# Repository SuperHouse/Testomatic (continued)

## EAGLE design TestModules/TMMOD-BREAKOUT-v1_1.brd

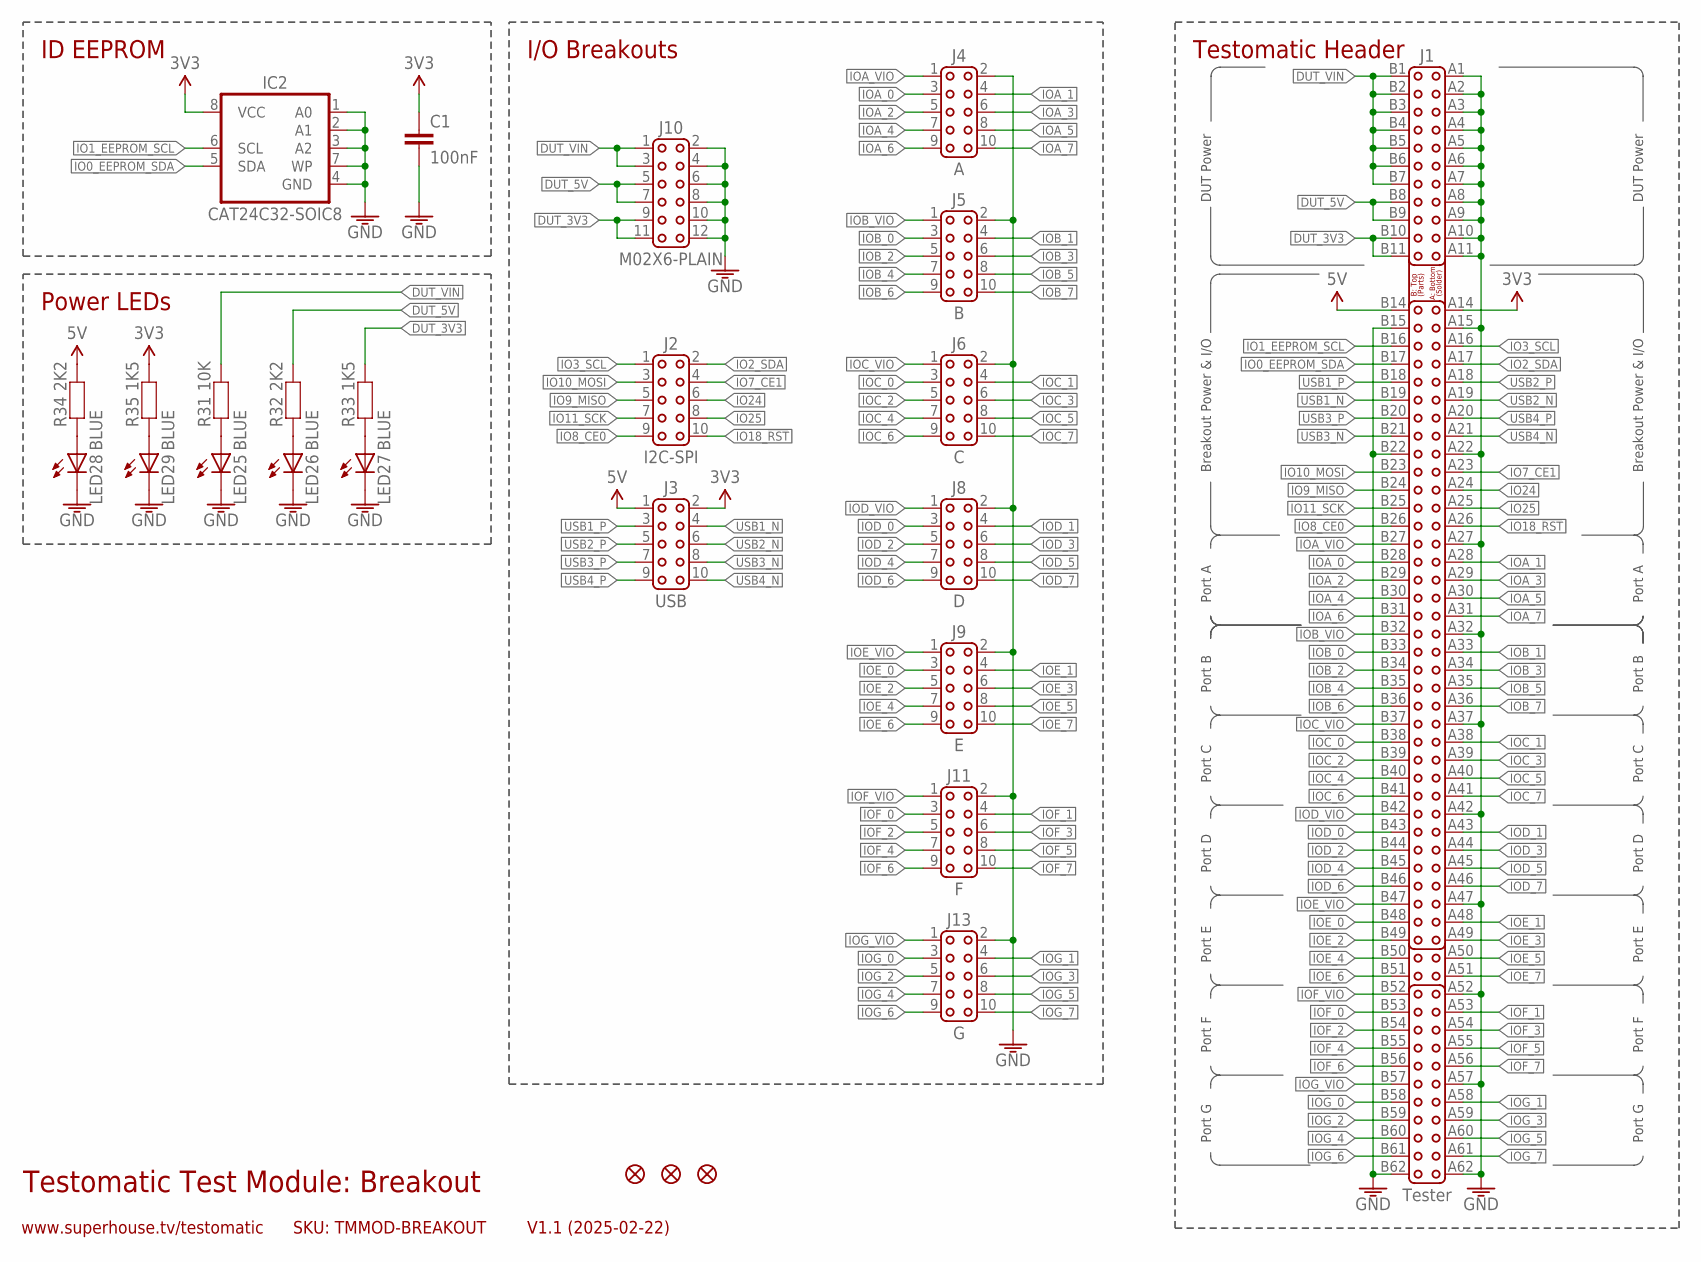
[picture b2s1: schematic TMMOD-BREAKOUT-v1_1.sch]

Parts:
C1: 100nF; C0603
FID1, FID2, FID3: FIDUCIAL1X2.5; FIDUCIAL-1X2.5
IC2: CAT24C32-SOIC8; SOIC8
J1: Tester; PCI-CARD
J2: I2C-SPI; 2X05-2.54-PLAIN
J3: USB; 2X05-2.54-PLAIN
J4: A; 2X05-2.54-PLAIN
J5: B; 2X05-2.54-PLAIN
J6: C; 2X05-2.54-PLAIN
J8: D; 2X05-2.54-PLAIN
J9: E; 2X05-2.54-PLAIN
J10: M02X6-PLAIN; 2X06
J11: F; 2X05-2.54-PLAIN
J13: G; 2X05-2.54-PLAIN
LED25, LED26, LED27, LED28, LED29: BLUE; LED-0603
R31: 10K; R0603
R32, R34: 2K2; R0603
R33, R35: 1K5; R0603

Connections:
3.3V: C1.1, IC2.8 (VCC), J1.A14, J3.2, R35.2
5V: J1.B14, J3.1, R34.2
DUT_3V3: J1.B10, J1.B11, J10.9, J10.11, R33.2
DUT_5V: J1.B8, J1.B9, J10.5, J10.7, R32.2
DUT_VIN: J1.B1, J1.B2, J1.B3, J1.B4, J1.B5, J1.B6, J1.B7, J10.1, J10.3, R31.2
GND: C1.2, IC2.1 (A0), IC2.2 (A1), IC2.3 (A2), IC2.4 (GND), IC2.7 (WP), J1.A1, J1.A2, J1.A3, J1.A4, J1.A5, J1.A6, J1.A7, J1.A8, J1.A9, J1.A10, J1.A11, J1.A15, J1.A22, J1.A27, J1.A32, J1.A37, J1.A42, J1.A47, J1.A52, J1.A57, J1.A62, J1.B15, J1.B22, J1.B62, J4.2, J5.2, J6.2, J8.2, J9.2, J10.2, J10.4, J10.6, J10.8, J10.10, J10.12, J11.2, J13.2, LED25.C, LED26.C, LED27.C, LED28.C, LED29.C
IO0_EEPROM_SDA: IC2.5 (SDA), J1.B17
IO1_EEPROM_SCL: IC2.6 (SCL), J1.B16
IO2_SDA: J1.A17, J2.2
IO3_SCL: J1.A16, J2.1
IO7_CE1: J1.A23, J2.4
IO8_CE0: J1.B26, J2.9
IO9_MISO: J1.B24, J2.5
IO10_MOSI: J1.B23, J2.3
IO11_SCK: J1.B25, J2.7
IO18_!RST: J1.A26, J2.10
IO24: J1.A24, J2.6
IO25: J1.A25, J2.8
IOA_0: J1.B28, J4.3
IOA_1: J1.A28, J4.4
IOA_2: J1.B29, J4.5
IOA_3: J1.A29, J4.6
IOA_4: J1.B30, J4.7
IOA_5: J1.A30, J4.8
IOA_6: J1.B31, J4.9
IOA_7: J1.A31, J4.10
IOA_VIO: J1.B27, J4.1
IOB_0: J1.B33, J5.3
IOB_1: J1.A33, J5.4
IOB_2: J1.B34, J5.5
IOB_3: J1.A34, J5.6
IOB_4: J1.B35, J5.7
IOB_5: J1.A35, J5.8
IOB_6: J1.B36, J5.9
IOB_7: J1.A36, J5.10
IOB_VIO: J1.B32, J5.1
IOC_0: J1.B38, J6.3
IOC_1: J1.A38, J6.4
IOC_2: J1.B39, J6.5
IOC_3: J1.A39, J6.6
IOC_4: J1.B40, J6.7
IOC_5: J1.A40, J6.8
IOC_6: J1.B41, J6.9
IOC_7: J1.A41, J6.10
IOC_VIO: J1.B37, J6.1
IOD_0: J1.B43, J8.3
IOD_1: J1.A43, J8.4
IOD_2: J1.B44, J8.5
IOD_3: J1.A44, J8.6
IOD_4: J1.B45, J8.7
IOD_5: J1.A45, J8.8
IOD_6: J1.B46, J8.9
IOD_7: J1.A46, J8.10
IOD_VIO: J1.B42, J8.1
IOE_0: J1.B48, J9.3
IOE_1: J1.A48, J9.4
IOE_2: J1.B49, J9.5
IOE_3: J1.A49, J9.6
IOE_4: J1.B50, J9.7
IOE_5: J1.A50, J9.8
IOE_6: J1.B51, J9.9
IOE_7: J1.A51, J9.10
IOE_VIO: J1.B47, J9.1
IOF_0: J1.B53, J11.3
IOF_1: J1.A53, J11.4
IOF_2: J1.B54, J11.5
IOF_3: J1.A54, J11.6
IOF_4: J1.B55, J11.7
IOF_5: J1.A55, J11.8
IOF_6: J1.B56, J11.9
IOF_7: J1.A56, J11.10
IOF_VIO: J1.B52, J11.1
IOG_0: J1.B58, J13.3
IOG_1: J1.A58, J13.4
IOG_2: J1.B59, J13.5
IOG_3: J1.A59, J13.6
IOG_4: J1.B60, J13.7
IOG_5: J1.A60, J13.8
IOG_6: J1.B61, J13.9
IOG_7: J1.A61, J13.10
IOG_VIO: J1.B57, J13.1
unnamed: LED25.A, R31.1
unnamed: LED28.A, R34.1
unnamed: LED26.A, R32.1
unnamed: LED27.A, R33.1
unnamed: LED29.A, R35.1
USB1_N: J1.B19, J3.4
USB1_P: J1.B18, J3.3
USB2_N: J1.A19, J3.6
USB2_P: J1.A18, J3.5
USB3_N: J1.B21, J3.8
USB3_P: J1.B20, J3.7
USB4_N: J1.A21, J3.10
USB4_P: J1.A20, J3.9

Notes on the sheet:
Testomatic Test Module: Breakout
V1.1 (2025-02-22)
www.superhouse.tv/testomatic
SKU: TMMOD-BREAKOUT
ID EEPROM
Testomatic Header
DUT Power
Breakout Power & I/O
Power LEDs
I/O Breakouts
Port A
Port B
Port G
Port F
Port E
Port D
Port C

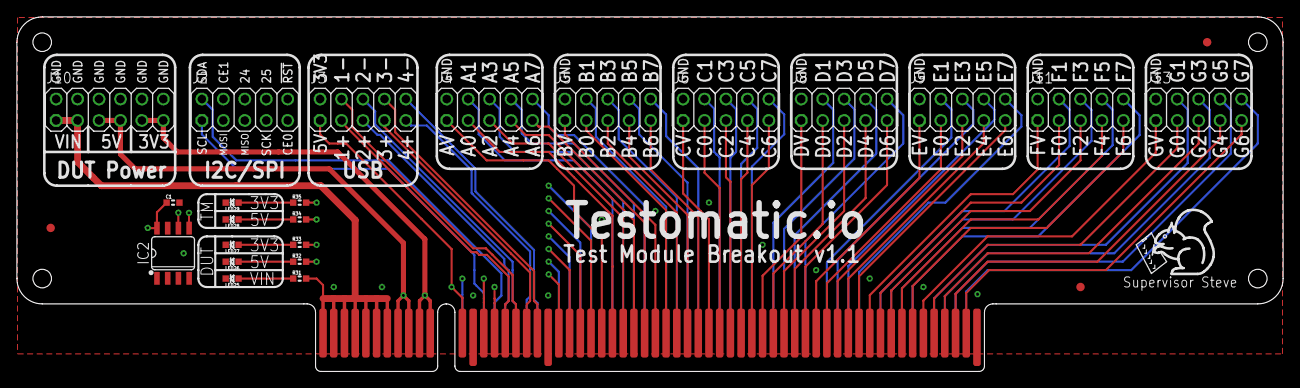
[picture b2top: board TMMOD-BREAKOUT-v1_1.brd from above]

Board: 4 copper layers, 150.0 x 42.0 mm, 26 parts (0 on the bottom side), 94 nets.

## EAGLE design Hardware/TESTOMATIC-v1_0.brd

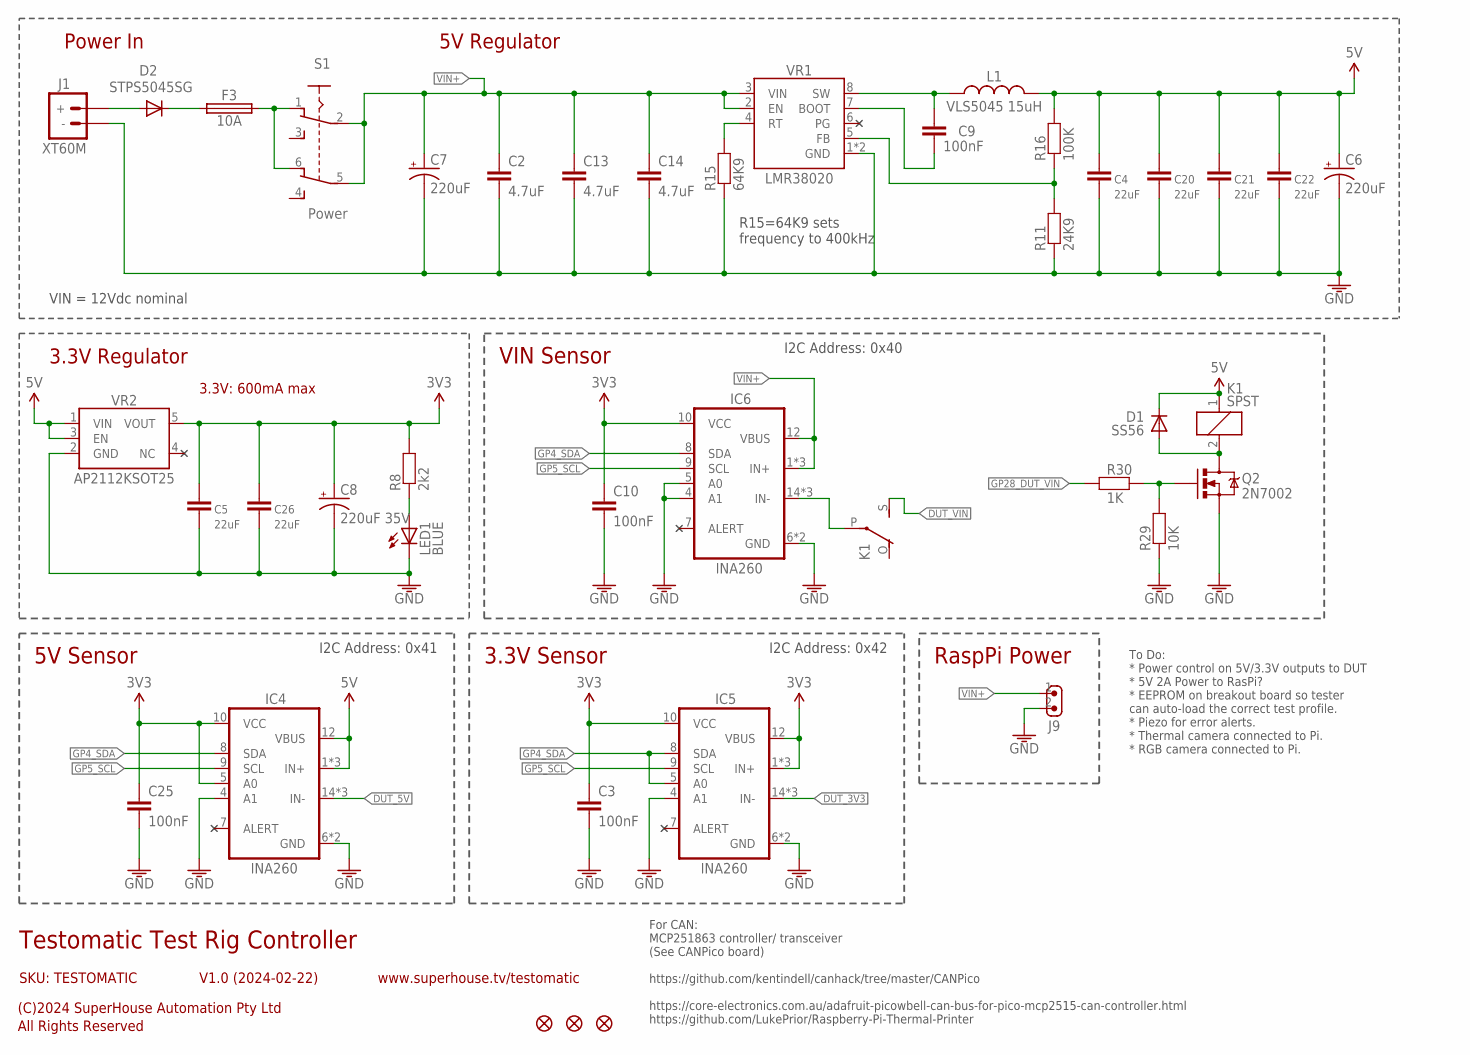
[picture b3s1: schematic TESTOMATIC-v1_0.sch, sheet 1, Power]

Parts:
C2, C13, C14: 4.7uF; C1206
C3, C9, C10, C25: 100nF; C0603
C4, C5, C20, C21, C22, C26: 22uF; C0805
C6, C7: 220uF; PANASONIC_G
C8: 220uF 35V; PANASONIC_G
D1: SS56; SMA-DIODE
D2: STPS5045SG; D2PACK
F3: 10A; MCCQ-122
FID1, FID2, FID3: FIDUCIAL1X2.5; FIDUCIAL-1X2.5
IC4, IC5, IC6: INA260; TSSOP-16
J1: XT60M; XT60PW-M
J9: M02-SCREW-3.81MM-VERT; SCREWTERMINAL-3.81MM-VERT-2
K1: SPST; G5LE
L1: VLS5045 15uH; INDUCTOR-5045
LED1: BLUE; LED-0603
Q2: 2N7002; SOT23-3
R8: 2k2; R0603
R11: 24K9; R0603
R15: 64K9; R0603
R16: 100K; R0603
R29: 10K; R0603
R30: 1K; R0603
S1: Power; 7201SD9AV2BE
VR1: LMR38020; HSOIC8
VR2: AP2112KSOT25; SOT23-5

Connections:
3.3V: C3.1, C5.1, C8.+, C10.1, C25.1, C26.1, IC4.5 (A0), IC4.10 (VCC), IC5.1 (IN+), IC5.2 (IN+), IC5.3 (IN+), IC5.10 (VCC), IC5.12 (VBUS), IC6.10 (VCC), R8.2, VR2.5 (VOUT); also elsewhere on the board
5V: C4.1, C6.+, C20.1, C21.1, C22.1, D1.C, IC4.1 (IN+), IC4.2 (IN+), IC4.3 (IN+), IC4.12 (VBUS), K1.1, L1.2, R16.2, VR2.1 (VIN), VR2.3 (EN); also elsewhere on the board
DUT_3V3: IC5.14 (IN-), IC5.15 (IN-), IC5.16 (IN-); also elsewhere on the board
DUT_5V: IC4.14 (IN-), IC4.15 (IN-), IC4.16 (IN-); also elsewhere on the board
DUT_VIN: K1.S (NO); also elsewhere on the board
GND: C2.2, C3.2, C4.2, C5.2, C6.-, C7.-, C8.-, C10.2, C13.2, C14.2, C20.2, C21.2, C22.2, C25.2, C26.2, IC4.4 (A1), IC4.6 (GND), IC4.11 (GND), IC5.4 (A1), IC5.6 (GND), IC5.11 (GND), IC6.4 (A1), IC6.5 (A0), IC6.6 (GND), IC6.11 (GND), J1.-, J9.2, LED1.C, Q2.2 (S), R11.1, R15.1, R29.1, VR1.1 (GND), VR1.TGND (GND), VR2.2 (GND); also elsewhere on the board
GP4_SDA: IC4.8 (SDA), IC5.5 (A0), IC5.8 (SDA), IC6.8 (SDA); also elsewhere on the board
GP5_SCL: IC4.9 (SCL), IC5.9 (SCL), IC6.9 (SCL); also elsewhere on the board
GP28_DUT_VIN: R30.1; also elsewhere on the board
unnamed: C9.1, L1.1, VR1.8 (SW)
unnamed: D2.2 (C), F3.1, F3.2 (1)
unnamed: R15.2, VR1.4 (RT)
unnamed: IC6.14 (IN-), IC6.15 (IN-), IC6.16 (IN-), K1.P (COM)
unnamed: D1.A, K1.2, Q2.3 (D)
unnamed: R11.2, R16.1, VR1.5 (FB)
unnamed: C9.2, VR1.7 (BOOT)
unnamed: LED1.A, R8.1
unnamed: Q2.1 (G), R29.2, R30.2
unnamed: F3.3 (2), F3.4 (2), S1.1, S1.6
unnamed: D2.1 (A), D2.3 (A), J1.+
PG: VR1.6 (PG)
VIN+: C2.1, C7.+, C13.1, C14.1, IC6.1 (IN+), IC6.2 (IN+), IC6.3 (IN+), IC6.12 (VBUS), J9.1, S1.2, S1.5, VR1.2 (EN), VR1.3 (VIN)

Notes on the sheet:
Testomatic Test Rig Controller
V1.0 (2024-02-22)
SKU: TESTOMATIC
(C)2024 SuperHouse Automation Pty Ltd
All Rights Reserved
www.superhouse.tv/testomatic
3.3V: 600mA max
VIN = 12Vdc nominal
5V Regulator
3.3V Regulator
Power In
R15=64K9 sets frequency to 400kHz
5V Sensor
I2C Address: 0x41
3.3V Sensor
I2C Address: 0x42
VIN Sensor
I2C Address: 0x40
For CAN: MCP251863 controller/ transceiver (See CANPico board) https://github.com/kentindell/canhack/tree/master/CANPico https://core-electronics.com.au/adafruit-picowbell-can-bus-for-pico-mcp2515-can-controller.html https://github.com/LukePrior/Raspberry-Pi-Thermal-Printer
To Do: * Power control on 5V/3.3V outputs to DUT * 5V 2A Power to RasPi? * EEPROM on breakout board so tester can auto-load the correct test profile. * Piezo for error alerts. * Thermal camera connected to Pi. * RGB camera connected to Pi.
RaspPi Power

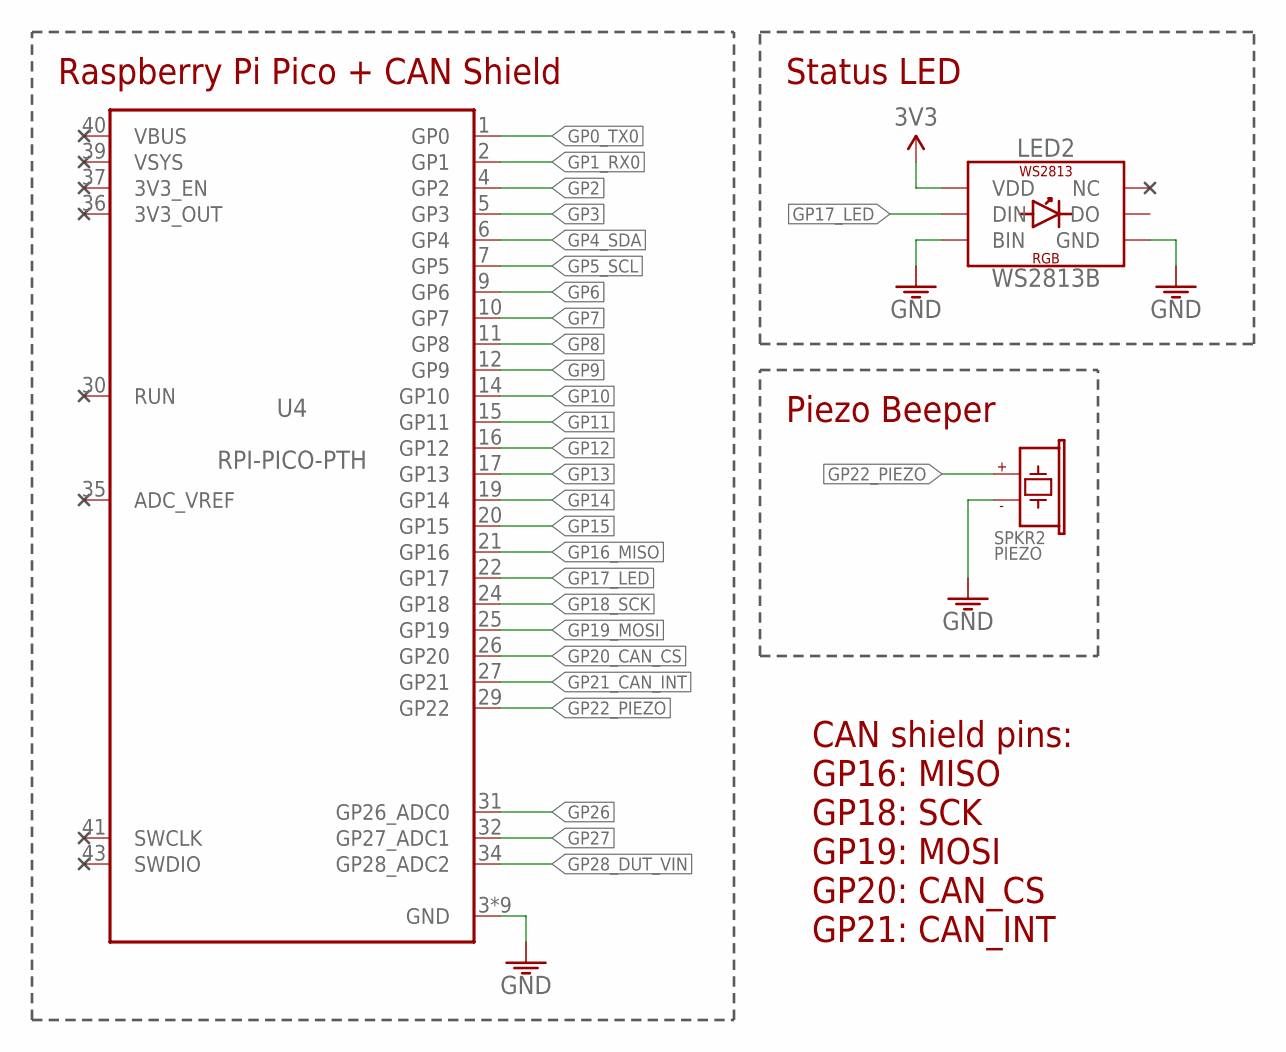
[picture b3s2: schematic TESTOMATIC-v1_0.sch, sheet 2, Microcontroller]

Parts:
LED2: WS2813B; WS2813
SPKR2: PIEZO; PIEZO-9.6X9.6-SMT
U4: RPI-PICO-PTH; PICO-PTH

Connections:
3.3V: LED2.2 (VDD); also elsewhere on the board
GND: LED2.5 (GND), LED2.6 (BIN), SPKR2.2 (-), U4.3 (GND), U4.8 (GND), U4.13 (GND), U4.18 (GND), U4.23 (GND), U4.28 (GND), U4.33 (GND), U4.38 (GND), U4.42 (GND); also elsewhere on the board
GP0_TX0: U4.1 (GP0); also elsewhere on the board
GP1_RX0: U4.2 (GP1); also elsewhere on the board
GP2: U4.4 (GP2); also elsewhere on the board
GP3: U4.5 (GP3); also elsewhere on the board
GP4_SDA: U4.6 (GP4); also elsewhere on the board
GP5_SCL: U4.7 (GP5); also elsewhere on the board
GP6: U4.9 (GP6); also elsewhere on the board
GP7: U4.10 (GP7); also elsewhere on the board
GP8: U4.11 (GP8); also elsewhere on the board
GP9: U4.12 (GP9); also elsewhere on the board
GP10: U4.14 (GP10); also elsewhere on the board
GP11: U4.15 (GP11); also elsewhere on the board
GP12: U4.16 (GP12); also elsewhere on the board
GP13: U4.17 (GP13); also elsewhere on the board
GP14: U4.19 (GP14); also elsewhere on the board
GP15: U4.20 (GP15); also elsewhere on the board
GP16_MISO: U4.21 (GP16)
GP17_LED: LED2.4 (DIN), U4.22 (GP17)
GP18_SCK: U4.24 (GP18)
GP19_MOSI: U4.25 (GP19)
GP20_CAN_CS: U4.26 (GP20)
GP21_CAN_INT: U4.27 (GP21)
GP22_PIEZO: SPKR2.1 (+), U4.29 (GP22)
GP26: U4.31 (GP26_ADC0); also elsewhere on the board
GP27: U4.32 (GP27_ADC1); also elsewhere on the board
GP28_DUT_VIN: U4.34 (GP28_ADC2); also elsewhere on the board
VBUS: U4.40 (VBUS)

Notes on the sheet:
Piezo Beeper
Status LED
CAN shield pins: GP16: MISO GP18: SCK GP19: MOSI GP20: CAN_CS GP21: CAN_INT
Raspberry Pi Pico + CAN Shield

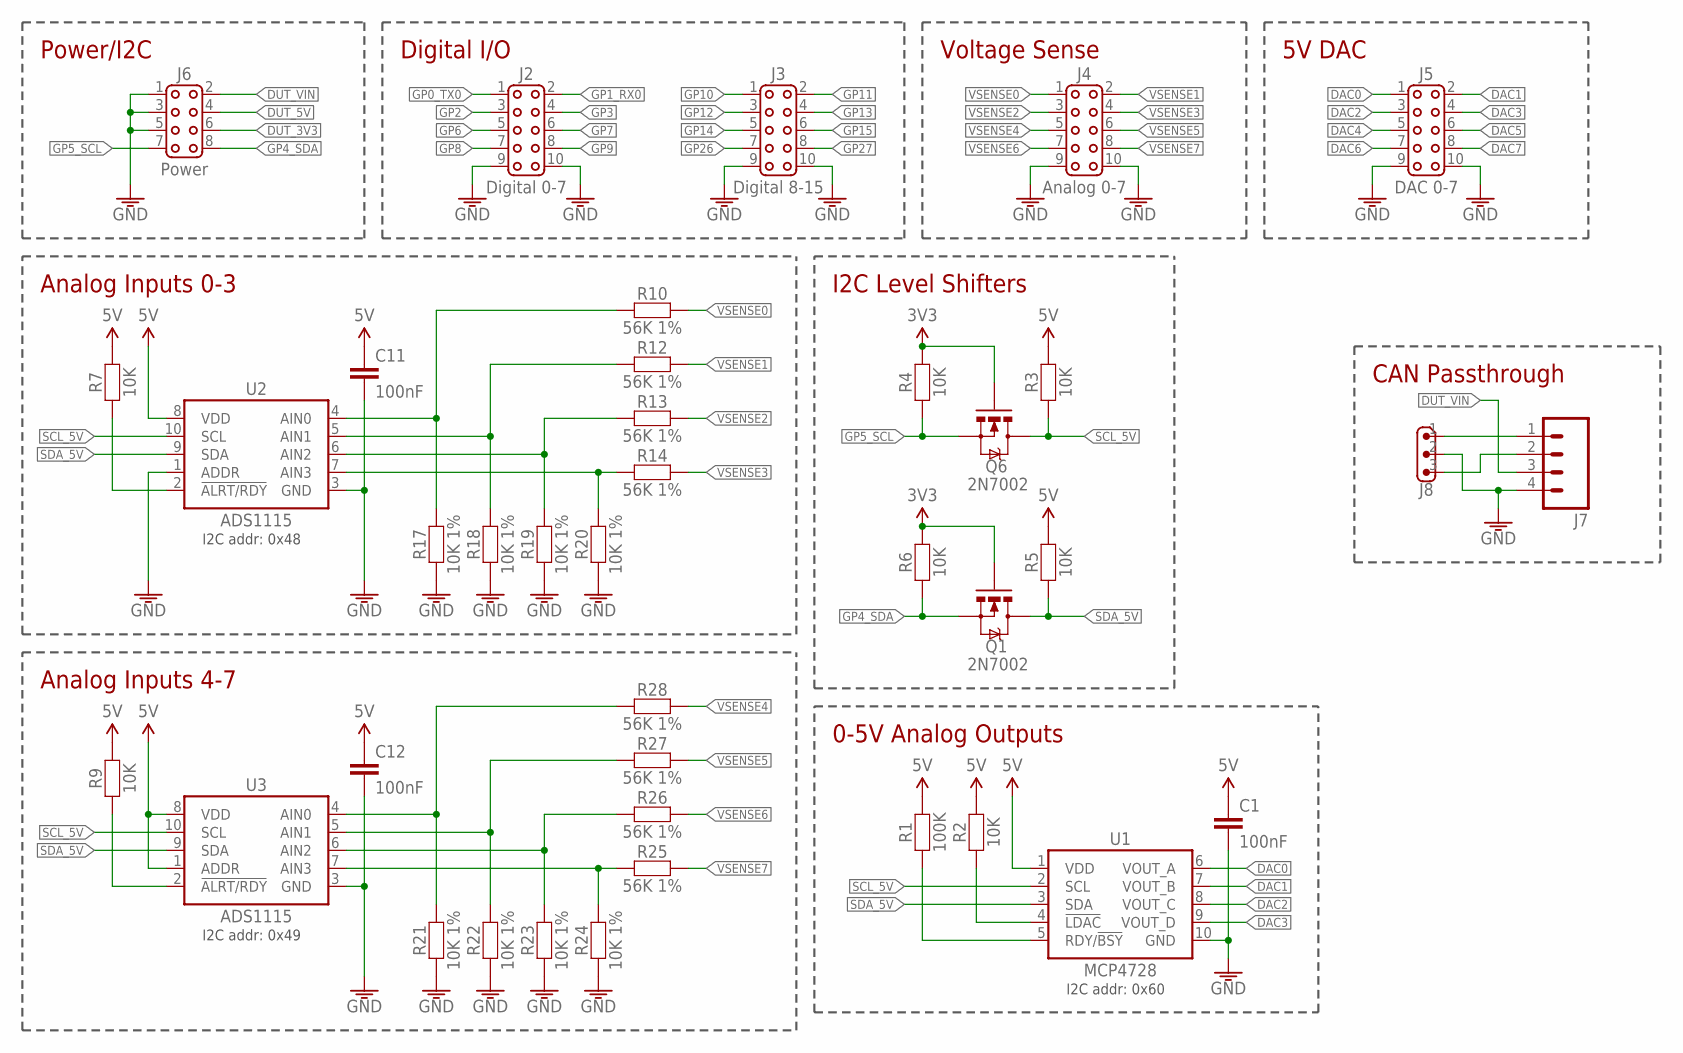
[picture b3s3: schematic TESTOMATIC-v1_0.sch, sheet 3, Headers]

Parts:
C1, C11, C12: 100nF; C0603
J2: Digital 0-7; 2X05-2.54-SHROUDED
J3: Digital 8-15; 2X05-2.54-SHROUDED
J4: Analog 0-7; 2X05-2.54-SHROUDED
J5: DAC 0-7; 2X05-2.54-SHROUDED
J6: Power; 2X04-2.54-SHROUDED
J7: M04-SCREW-3.81MM-VERT-PLUG; SCREWTERMINAL-3.81MM-VERT-4
J8: M03-SCREW-3.5MM; SCREWTERMINAL-3.5MM-3
Q1, Q6: 2N7002; SOT23-3
R1: 100K; R0603
R2, R3, R4, R5, R6, R7, R9: 10K; R0603
R10, R12, R13, R14, R25, R26, R27, R28: 56K 1%; R0603
R17, R18, R19, R20, R21, R22, R23, R24: 10K 1%; R0603
U1: MCP4728; MSOP10
U2, U3: ADS1115; MSOP10

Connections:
3.3V: Q1.1 (G), Q6.1 (G), R4.2, R6.2; also elsewhere on the board
5V: C1.1, C11.1, C12.1, R1.2, R2.2, R3.2, R5.2, R7.2, R9.2, U1.1 (VDD), U2.8 (VDD), U3.1 (ADDR), U3.8 (VDD); also elsewhere on the board
DAC0: J5.1, U1.6 (VOUT_A)
DAC1: J5.2, U1.7 (VOUT_B)
DAC2: J5.3, U1.8 (VOUT_C)
DAC3: J5.4, U1.9 (VOUT_D)
DAC4: J5.5
DAC5: J5.6
DAC6: J5.7
DAC7: J5.8
DUT_3V3: J6.6; also elsewhere on the board
DUT_5V: J6.4; also elsewhere on the board
DUT_VIN: J6.2, J7.3; also elsewhere on the board
GND: C1.2, C11.2, C12.2, J2.9, J2.10, J3.9, J3.10, J4.9, J4.10, J5.9, J5.10, J6.1, J6.3, J6.5, J7.4, J8.2, R17.1, R18.1, R19.1, R20.1, R21.1, R22.1, R23.1, R24.1, U1.10 (GND), U2.1 (ADDR), U2.3 (GND), U3.3 (GND); also elsewhere on the board
GP0_TX0: J2.1; also elsewhere on the board
GP1_RX0: J2.2; also elsewhere on the board
GP2: J2.3; also elsewhere on the board
GP3: J2.4; also elsewhere on the board
GP4_SDA: J6.8, Q1.2 (S), R6.1; also elsewhere on the board
GP5_SCL: J6.7, Q6.2 (S), R4.1; also elsewhere on the board
GP6: J2.5; also elsewhere on the board
GP7: J2.6; also elsewhere on the board
GP8: J2.7; also elsewhere on the board
GP9: J2.8; also elsewhere on the board
GP10: J3.1; also elsewhere on the board
GP11: J3.2; also elsewhere on the board
GP12: J3.3; also elsewhere on the board
GP13: J3.4; also elsewhere on the board
GP14: J3.5; also elsewhere on the board
GP15: J3.6; also elsewhere on the board
GP26: J3.7; also elsewhere on the board
GP27: J3.8; also elsewhere on the board
unnamed: R7.1, U2.2 (!ALRT/RDY)
unnamed: R10.1, R17.2, U2.4 (AIN0)
unnamed: R12.1, R18.2, U2.5 (AIN1)
unnamed: R13.1, R19.2, U2.6 (AIN2)
unnamed: R14.1, R20.2, U2.7 (AIN3)
unnamed: R21.2, R28.1, U3.4 (AIN0)
unnamed: R22.2, R27.1, U3.5 (AIN1)
unnamed: R23.2, R26.1, U3.6 (AIN2)
unnamed: R24.2, R25.1, U3.7 (AIN3)
unnamed: R9.1, U3.2 (!ALRT/RDY)
unnamed: J7.1, J8.1
unnamed: J7.2, J8.3
unnamed: R2.1, U1.4 (!LDAC)
unnamed: R1.1, U1.5 (RDY/!BSY)
SCL_5V: Q6.3 (D), R3.1, U1.2 (SCL), U2.10 (SCL), U3.10 (SCL)
SDA_5V: Q1.3 (D), R5.1, U1.3 (SDA), U2.9 (SDA), U3.9 (SDA)
VSENSE0: J4.1, R10.2
VSENSE1: J4.2, R12.2
VSENSE2: J4.3, R13.2
VSENSE3: J4.4, R14.2
VSENSE4: J4.5, R28.2
VSENSE5: J4.6, R27.2
VSENSE6: J4.7, R26.2
VSENSE7: J4.8, R25.2

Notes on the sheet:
Power/I2C
Digital I/O
Voltage Sense
5V DAC
I2C Level Shifters
0-5V Analog Outputs
Analog Inputs 0-3
I2C addr: 0x48
I2C addr: 0x49
I2C addr: 0x60
Analog Inputs 4-7
CAN Passthrough

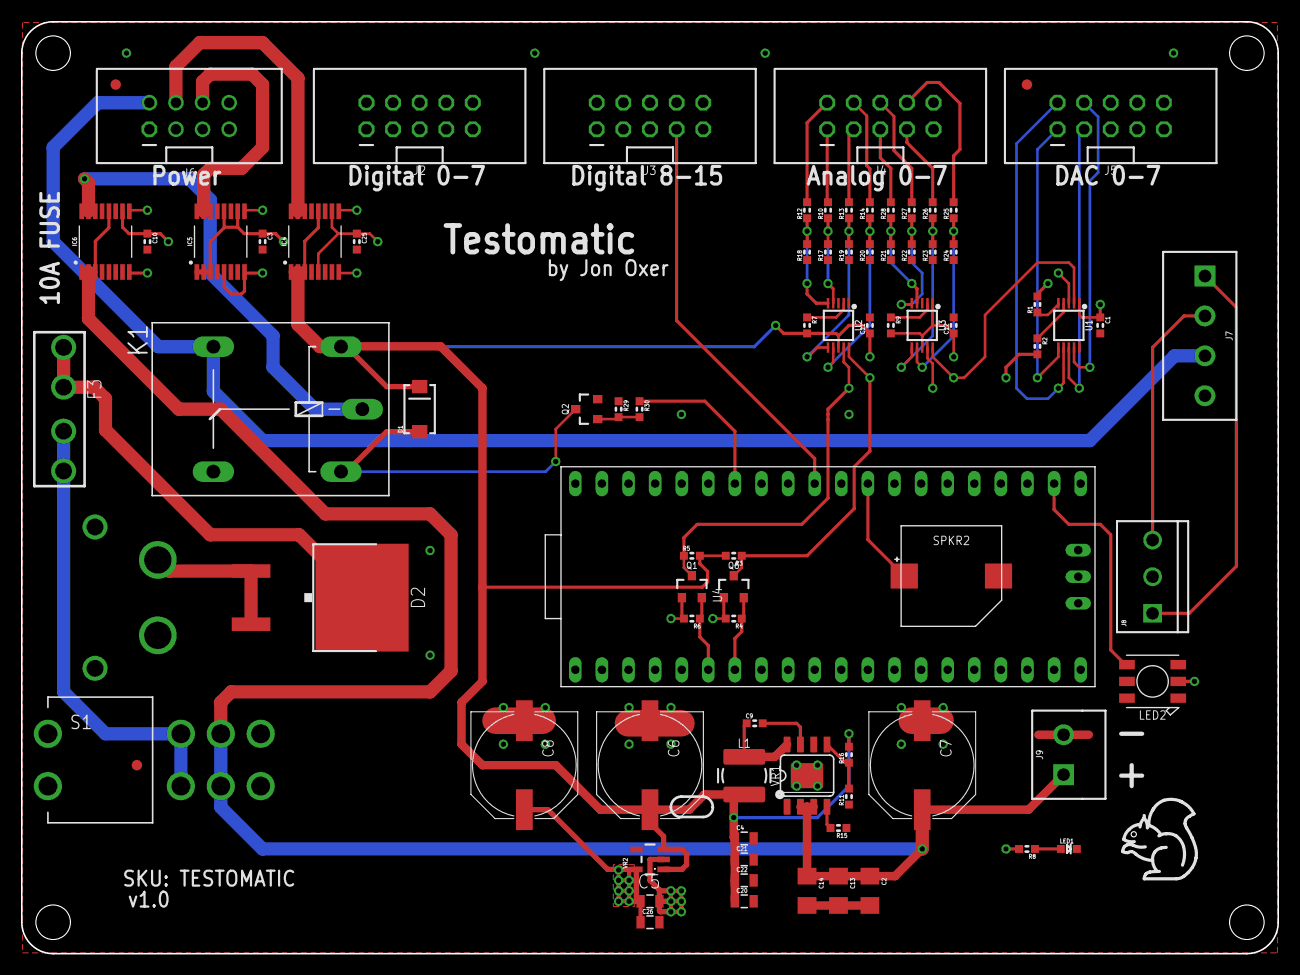
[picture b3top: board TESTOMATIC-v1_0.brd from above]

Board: 4 copper layers, 120.0 x 89.0 mm, 82 parts (0 on the bottom side), 67 nets.

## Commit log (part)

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2024-06-25 Initial import
2024-07-28 Added pin allocations document.
2024-07-28 Added notes about CAN bus.
2024-08-22 Added v2.0 hardware files and annotated images.
2024-08-22 Expanded README and added overview image.
2024-08-22 Fixed GPIO voltage in docs.
2024-08-23 Added rough draft of documentation for creating a Test Module.
2024-08-23 Added screenshots to module guide.
2024-08-23 Syntax improvements.
2024-08-23 Images swapped
2024-08-23 Added image of test module.
2024-08-25 Replaced render of v2 with photo of prototype.
2024-08-26 Added links to YouTube channel and Discord for discussion of design.
2024-08-26 Updates to notes and readme, added to-do list
2024-09-02 Added To Do items from the last livestream.
2025-02-22 Updated design files and documentation for v2.2 release.
2025-02-23 Updates to improve clearance of I/O modules and lower chassis deck.
2025-03-06 Added pic of assembled v2.2 board.
2025-03-06 Added v2.2 design files in Eagle format.
2025-03-06 Fixed reference to images.
2025-03-31 Added design files for test module breakout and mechanicals.
2025-03-31 Added reference material for devices that may interface with Testomatic
2025-03-31 Fixed paths to images.
2025-04-13 Added chassis design files.
2025-04-13 Added reference to I/O Module.
2025-04-13 Typo
2025-09-24 Updated README to reflect newest v2.3 hardware.
2025-09-24 Added v2.3 design files and images.
2025-12-05 Added link to UPDI programmer module
2025-12-30 Added designs for LED colour sensor shrouds
2026-02-02 Replaced image of v1 chassis with v2
2026-06-21 Added link to video of Testomatic talk at Everything Open 2026
2026-06-22 Added link to the Register with a screenshot
